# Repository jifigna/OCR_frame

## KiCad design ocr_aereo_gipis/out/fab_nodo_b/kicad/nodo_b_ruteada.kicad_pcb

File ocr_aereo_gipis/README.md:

# OCR Aéreo — versión GIPIS (definitiva, 2026-10-20)

Placa del nodo aéreo/bote: Heltec WiFi LoRa 32 V4 + OCR 0222 Ed (por UART MUX 2 click)
+ PAR 231 (por ADS1115) + inclinación (ICM-20689) + respaldo en microSD + alimentación
de batería de 12 V con buck D-SUN. Para la campaña CONAE (SABIA-Mar), octubre 2026.

Diseñada para fabricar en la **LPKF ProtoMat S63** del laboratorio: **una sola cara**
(todo el cobre abajo, B.Cu), **sin puentes**, sin metalizado. Los zócalos se sueldan
solo del lado del cobre.

| | |
|---|---|
| Placa | 104 × 90 mm, FR4 1,6 mm |
| Pistas | 0,92 mm (señal) / 1,38 mm (potencia), mínimo 0,8 |
| Aislación | 0,6 mm entre pistas, 0,5 mm entre plano de GND y pistas |
| Borde | 1 mm |
| DRC | 0 errores, 0 pads sin conectar, esquemático ↔ PCB en paridad |

## Conexiones principales

- **I2C en GPIO17/18** (bus del OLED, como en el protoboard), por los pads auxiliares
  de la V4 en el extremo opuesto al USB, del lado de J2. ADS1115 en 0x48, ICM-20689
  en 0x68 (AD0 a GND).
- **OCR**: TX del click → GPIO6 (J3.17). Click en canal 1 (A0/A1 a GND).
- **microSD (HW-125, 5 V)**: CS 42, SCK 41, MOSI 40, MISO 39.
- **Alimentación**: 12 V → fusible → 1N5819 → D-SUN (~5,3 V) → JP1 → 1N5819 → +5V
  (Heltec y SD). ADS1115 desde Ve; ICM y click desde 3V3 (J3.3).
- **Borneras** de 2 polos, paso 5,08: J1 batería, J2 alimentación del OCR,
  J3 alimentación del PAR, J4 señal del PAR. La bornera del click da al borde izquierdo.

## Antes de fresar

Imprimir `out/fab_nodo_b/plantilla_1a1_armado.pdf` al 100 % (sin "ajustar a página")
y apoyar los módulos reales. **Sin medir todavía**: la posición de los pads auxiliares
GPIO17/18 de la Heltec y el paso de las borneras. Ver `out/fab_nodo_b/LEEME.txt`.

## Archivos

- `nodo_b_ruteada.kicad_pro` — proyecto KiCad 10 (PCB ruteado + esquemático + librerías
  del proyecto `nodo_b.pretty` / `nodo_b.kicad_sym` + modelos 3D en `3d/`).
- `out/fab_nodo_b/` (y `.zip`) — paquete de fabricación: Gerber, Excellon, plantillas 1:1,
  LEEME con mechas.
- `out/` — esquemático en PDF, imágenes del ruteo y 3D, reporte de DRC.

## Regenerar

Todo sale de scripts (no editar el PCB a mano: se pisa al regenerar):

```
./make.sh
```

`gen_board.py` (ubicación, footprints y pre-ruteos fijos) → `route.py` (Freerouting:
una cara, GND ruteado) → `plano_gnd.py` → `gen_sch.py` + `finalizar.py` (esquemático
y librerías) → DRC → `fab_javi.py` (paquete de fabricación). Requiere KiCad 10 con
Python (`pcbnew`), Java y Freerouting 2.4.1 (`FREEROUTING_JAR` para indicar dónde está
el `.jar`; por defecto `~/.local/share/freerouting/freerouting-2.4.1.jar`).

GIPIS — UNPSJB.

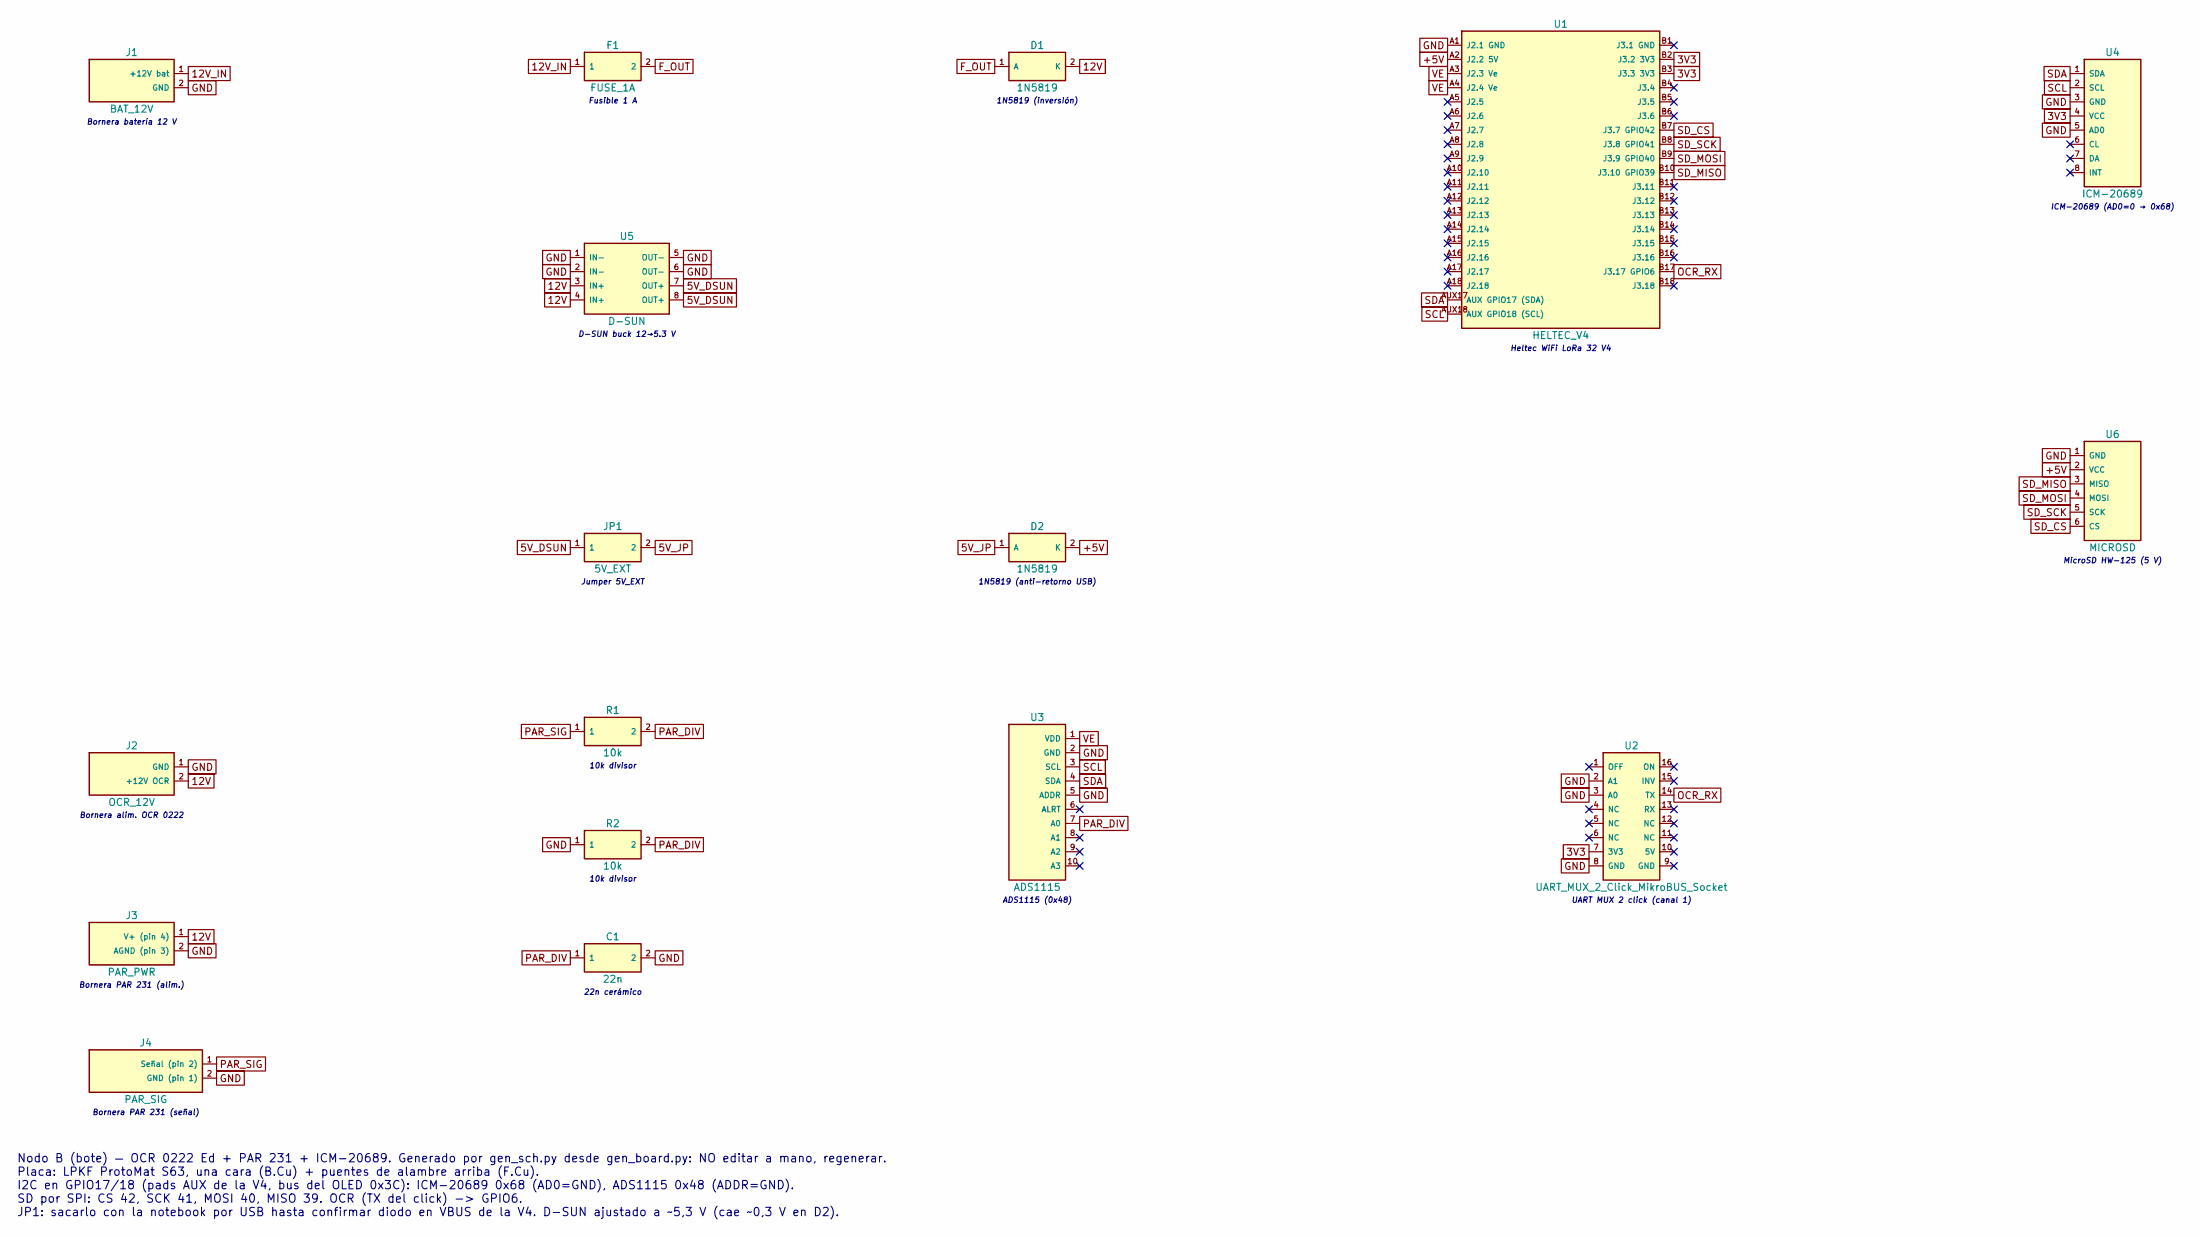
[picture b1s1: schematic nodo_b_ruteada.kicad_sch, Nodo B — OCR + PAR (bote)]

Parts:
C1: 22n
D1, D2: 1N5819
F1: FUSE_1A
J1: BAT_12V
J2: OCR_12V
J3: PAR_PWR
J4: PAR_SIG
JP1: 5V_EXT
R1, R2: 10k
U1: HELTEC_V4
U2: UART_MUX_2_Click_MikroBUS_Socket
U3: ADS1115
U4: ICM-20689
U5: D-SUN
U6: MICROSD

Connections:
3V3: U1.B2 (J3.2 3V3), U1.B3 (J3.3 3V3), U2.7 (3V3), U4.4 (VCC)
5V_DSUN: JP1.1, U5.7 (OUT+), U5.8 (OUT+)
5V_JP: D2.1 (A), JP1.2
12V: D1.2 (K), J2.2 (+12V OCR), J3.1 (V+ (pin 4)), U5.3 (IN+), U5.4 (IN+)
12V_IN: F1.1, J1.1 (+12V bat)
+5V: D2.2 (K), U1.A2 (J2.2 5V), U6.2 (VCC)
F_OUT: D1.1 (A), F1.2
GND: C1.2, J1.2 (GND), J2.1 (GND), J3.2 (AGND (pin 3)), J4.2 (GND (pin 1)), R2.1, U1.A1 (J2.1 GND), U2.2 (A1), U2.3 (A0), U2.8 (GND), U3.2 (GND), U3.5 (ADDR), U4.3 (GND), U4.5 (AD0), U5.1 (IN−), U5.2 (IN−), U5.5 (OUT−), U5.6 (OUT−), U6.1 (GND)
OCR_RX: U1.B17 (J3.17 GPIO6), U2.14 (TX)
PAR_DIV: C1.1, R1.2, R2.2, U3.7 (A0)
PAR_SIG: J4.1 (Señal (pin 2)), R1.1
SCL: U1.AUX18 (AUX GPIO18 (SCL)), U3.3 (SCL), U4.2 (SCL)
SDA: U1.AUX17 (AUX GPIO17 (SDA)), U3.4 (SDA), U4.1 (SDA)
SD_CS: U1.B7 (J3.7 GPIO42), U6.6 (CS)
SD_MISO: U1.B10 (J3.10 GPIO39), U6.3 (MISO)
SD_MOSI: U1.B9 (J3.9 GPIO40), U6.4 (MOSI)
SD_SCK: U1.B8 (J3.8 GPIO41), U6.5 (SCK)
VE: U1.A3 (J2.3 Ve), U1.A4 (J2.4 Ve), U3.1 (VDD)

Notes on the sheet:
Nodo B (bote) — OCR 0222 Ed + PAR 231 + ICM-20689. Generado por gen_sch.py desde gen_board.py: NO editar a mano, regenerar. Placa: LPKF ProtoMat S63, una cara (B.Cu) + puentes de alambre arriba (F.Cu). I2C en GPIO17/18 (pads AUX de la V4, bus del OLED 0x3C): ICM-20689 0x68 (AD0=GND), ADS1115 0x48 (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
Bornera batería 12 V
Fusible 1 A
1N5819 (inversión)
Bornera alim. OCR 0222
Bornera PAR 231 (alim.)
Bornera PAR 231 (señal)
10k divisor
22n cerámico
ADS1115 (0x48)
D-SUN buck 12→5.3 V
Jumper 5V_EXT
1N5819 (anti-retorno USB)
Heltec WiFi LoRa 32 V4
ICM-20689 (AD0=0 → 0x68)
UART MUX 2 click (canal 1)
MicroSD HW-125 (5 V)

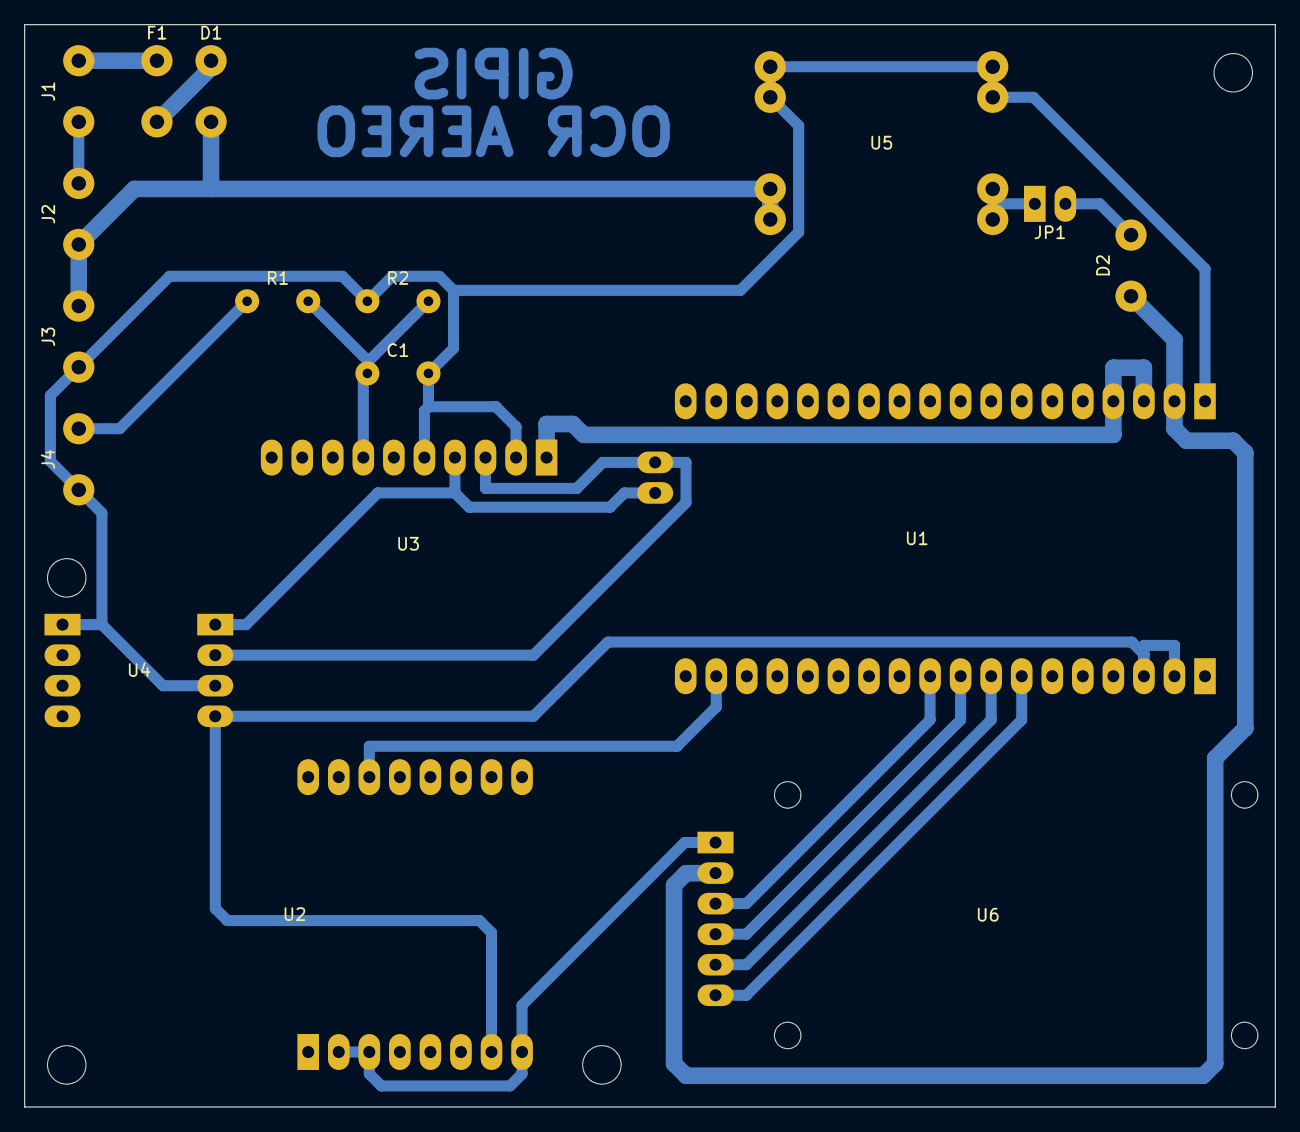
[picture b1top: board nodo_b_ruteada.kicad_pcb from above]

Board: 2 copper layers, 104.0 x 90.0 mm, 21 parts (0 on the bottom side), 18 nets.

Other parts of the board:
H1, H2, H3, H4: M3

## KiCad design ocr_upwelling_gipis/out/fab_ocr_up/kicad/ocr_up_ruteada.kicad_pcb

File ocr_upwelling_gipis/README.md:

# OCR Upwelling — versión GIPIS v2 (2026-10-20)

Placa del nodo del frame (OCR que mira al mar, Lu): Heltec WiFi LoRa 32 V4 + OCR por
RS-232 (MAX3232) + inclinación (ICM-20689 y GY-511) + RTC (ZS-042) + respaldo en microSD
+ buck desde la batería de 12 V. Campaña CONAE (SABIA-Mar), octubre 2026.

Parte de la placa de Juan (`OCR_AEREO_HELTEC_V1` en `main`): misma placa de 109,5 × 85,5 mm
y misma ubicación de módulos, con las correcciones de la revisión
(`REVISION_placa_juan_20261020.md`) y **sin relés ni BioShutter** (el OCR toma 12 V directo).

Para la **LPKF ProtoMat S63** del laboratorio: **una sola cara** (todo el cobre abajo),
sin metalizado, sin vías. Lo que no se puede rutear en una cara va con **8 puentes de
alambre W1–W8** (componentes de 2 pads; en el esquemático y en la plantilla).

| | |
|---|---|
| Pistas | 0,92 mm (señal) / 1,38 mm (potencia), mínimo 0,65 entre pines vecinos |
| Aislación | 0,6 mm entre pistas, 0,5 mm entre plano de GND y pistas, borde 1 mm |
| DRC | 0 errores, 0 pads sin conectar, esquemático ↔ PCB en paridad |

## Cambios respecto de la placa de Juan

- Tiras de la Heltec a 22,86 mm y alineadas (estaban a 23,00 y corridas 0,5 mm).
- I2C en GPIO17/18 (pads AUX del lado de J2), como en el protoboard.
- SD en GPIO 39–42 (CS 42, SCK 41, MOSI 40, MISO 39): el 21 es el reset del OLED y el 26
  lo usa la PSRAM.
- ICM-20689 con AD0 a Vext → 0x69 (en 0x68 chocaba con el DS3231) y tiras a 12,70 mm.
- MAX3232 girado 180°; T2IN a GND. UART: GPIO5 → T1IN, R1OUT → GPIO6.
- Fusible a la ENTRADA de los 12 V; D1 Schottky 1N5822; zener 1N5339B (5,6 V) sobre +5V;
  C7 470 µF con footprint de Ø8.
- Buck: J11 IN+, J10 IN− (GND), J8 OUT+ (5 V), J9 OUT− (GND).
- +5V → JP1 → D3 1N5819 → pin 5V de la Heltec (sacar JP1 con la Heltec por USB).
- Borneras Phoenix MCV 5,08: J7 batería (abajo) y J6 OCR en el borde derecho
  (de arriba a abajo GND, RX, TX, +12V).

## Antes de fresar

Imprimir `out/fab_ocr_up/plantilla_1a1_armado.pdf` al 100 % y apoyar los módulos reales.
Sin medir todavía: los pads AUX 17/18 de la Heltec, el orden de pines de la SD (Juan tenía
GND arriba) y del GY-511. Ver `out/fab_ocr_up/LEEME.txt`.

## Regenerar

Todo sale de scripts (no editar el PCB a mano: se pisa al regenerar): `./make.sh`.
`gen_board.py` (ubicación, footprints y pre-ruteos fijos) → `route.py` (Freerouting) →
`plano_gnd.py` → `fix_islas.py` → `convertir_alambres.py` (los tramos de arriba pasan a ser
puentes de alambre W6…, con `jumper_pad_groups`) → `esquema.py` / `gen_sch.py` /
`finalizar.py` → DRC → `fab_javi.py`. Requiere KiCad 10 con Python (`pcbnew`) y
Freerouting 2.4.1 (Java 25). `FREEROUTING_HOST=usuario@host` corre Freerouting en otra
máquina por SSH (en un contenedor `eclipse-temurin:25-jre`); vacío, lo corre local.

GIPIS — UNPSJB.

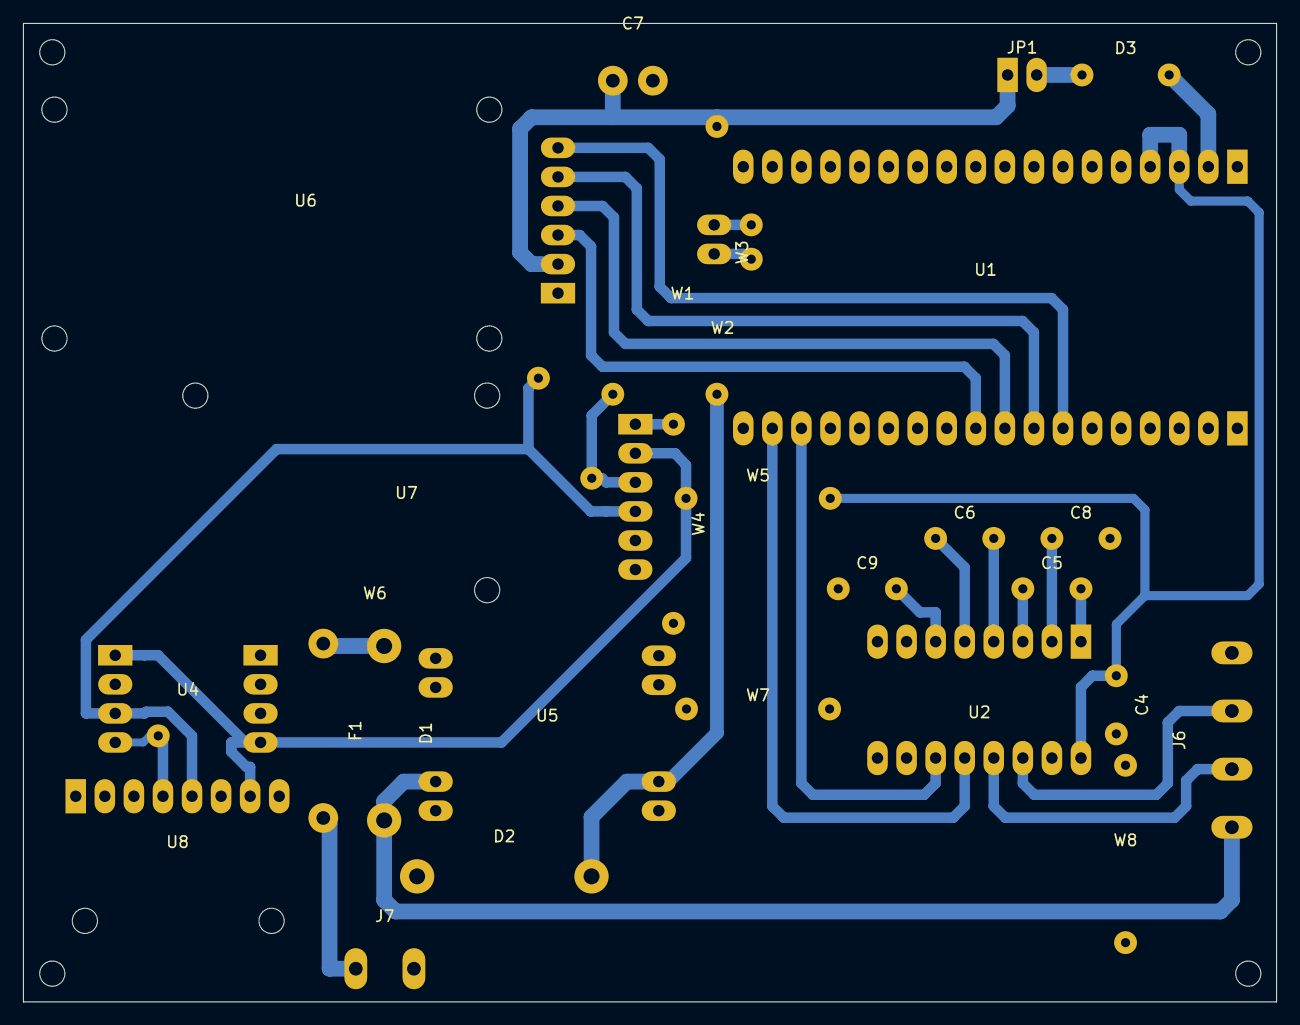
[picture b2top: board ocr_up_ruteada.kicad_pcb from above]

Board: 2 copper layers, 109.5 x 85.5 mm, 32 parts (0 on the bottom side), 29 nets.

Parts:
C4, C5, C6, C8, C9: 100n
C7: 470uF
D1: 1N5822
D2: 1N5339B
D3: 1N5819
F1: FUSE_2A
H1, H2, H3, H4: M2
J6: OCR
J7: BATERIA
JP1: 5V_EXT
U1: HELTEC_V4
U2: MAX3232
U4: ICM-20689
U5: BUCK
U6: MICROSD
U7: RTC_ZS-042
U8: GY-511
W1: PUENTE_SCL
W2: PUENTE_SDA
W3: PUENTE_5V
W4: PUENTE_GND
W5: PUENTE_VE
W6, W7, W8: ALAMBRE

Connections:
5V_HEL: D3.2, U1.A2
5V_JP: D3.1, JP1.2
5V_TOP: C7.1, JP1.1, U6.2, W3.1
12V: D1.2, J6.4, U5.3
+5V: D2.1, U5.7, W3.2
BATERIA: F1.2, J7.2
F_OUT: D1.1, F1.1
GND: C4.2, C7.2, C8.2, C9.1, D2.2, J6.1, J7.1, U1.A1, U2.10, U2.15, U4.2, U5.6, U6.1, U8.6, W4.2, W7.1, W7.2, W8.1, W8.2
GND_RTC: U7.1, W4.1
H_RX: U1.B17, U2.12
H_TX: U1.B16, U2.11
MAX_C1N: C5.1, U2.3
MAX_C1P: C5.2, U2.1
MAX_C2N: C6.1, U2.5
MAX_C2P: C6.2, U2.4
MAX_VSN: C9.2, U2.6
MAX_VSP: C8.1, U2.2
RX_OCR: J6.2, U2.14
SCL: U1.AUX18, W1.1
SCL_B: U4.3, U7.4, U8.5, W1.2
SDA: U1.AUX17, W2.1
SDA_B: U4.4, U7.3, U8.4, W2.2, W6.1, W6.2
SD_CS: U1.B7, U6.6
SD_MISO: U1.B10, U6.3
SD_MOSI: U1.B9, U6.4
SD_SCK: U1.B8, U6.5
TX_OCR: J6.3, U2.13
VE: C4.1, U1.A3, U1.A4, U2.16, W5.1
VE_B: U4.1, U4.8, U7.2, U8.7, W5.2

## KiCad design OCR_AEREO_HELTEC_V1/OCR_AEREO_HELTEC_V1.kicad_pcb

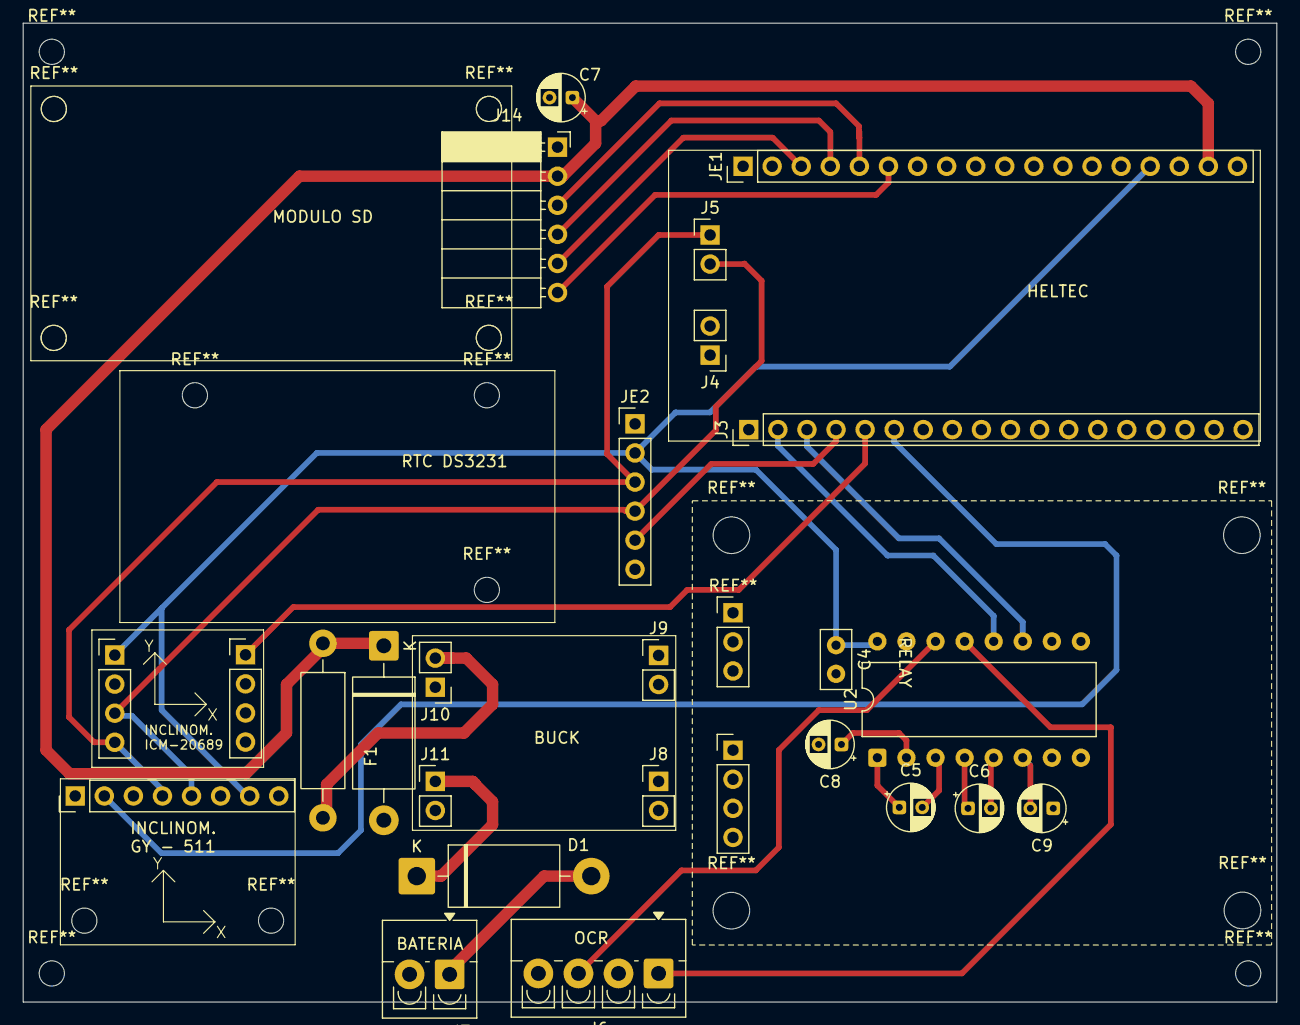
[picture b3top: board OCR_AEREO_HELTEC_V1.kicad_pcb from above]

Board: 2 copper layers, 109.5 x 85.5 mm, 26 parts (0 on the bottom side), 25 nets.

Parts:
C4: 0.1 uF; C_Disc_D5.0mm_W2.5mm_P2.50mm
C5, C6, C8, C9: 0.1uF; CP_Radial_D4.0mm_P2.00mm
C7: 470uF; CP_Radial_D4.0mm_P2.00mm
D1: 1N5402; D_DO-201AD_P15.24mm_Horizontal
D2: 1N53xxB; D_DO-201_P15.24mm_Horizontal
F1: Fuse; R_Axial_DIN0411_L9.9mm_D3.6mm_P15.24mm_Horizontal
J1, J1#2, J2: Conn_01x04_Socket; PinHeader_1x04_P2.54mm_Vertical
J3: Conn_01x18_Pin; PinHeader_1x18_P2.54mm_Vertical
J4, J5, J8, J9, J10, J11: Conn_01x02_Pin; PinHeader_1x02_P2.54mm_Vertical
J6: OCR; TerminalBlock_4Ucon_1x04_P3.50mm_Vertical
J7: BATERÍA; TerminalBlock_4Ucon_1x02_P3.50mm_Vertical
J12: Conn_01x08_Socket; PinHeader_1x08_P2.54mm_Vertical
J14: MODULO SD; PinSocket_1x06_P2.54mm_Horizontal
JE1: Conn_01x18_Pin; PinHeader_1x18_P2.54mm_Vertical
JE2: RTC_DS3231; PinHeader_1x06_P2.54mm_Vertical
U2: MAX3232; DIP-16_W10.16mm

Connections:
5V: C7.1, D2.1 (K), F1.1, J14.2, JE1.17
BATERIA: D1.2 (A), J7.1
CLK_SPI: J14.5, JE1.3
CS_SD: J14.6, JE1.6
GND: C4.2, C7.2, C8.2, C9.1, D2.2 (A), J1#2.2, J2.4, J3.18, J6.2, J7.2, J8.1 (Pin_1_1), J9.2 (Pin_2_2), J12.6, J14.1, JE2.1, U2.15 (GND)
HELTEC_TO_OCR: J3.3, U2.11 (T1IN)
INT_INCL_1: J2.1, J3.5
INT_INCL_2: J3.6, J12.2
IN_BUCK: D1.1 (K), J11.1 (Pin_1_1)
MISO: J14.3, JE1.5
MOSI: J14.4, JE1.4
unnamed: C5.1, U2.1 (C1+)
unnamed: C5.2, U2.3 (C1-)
unnamed: C6.1, U2.4 (C2+)
unnamed: C6.2, U2.5 (C2-)
unnamed: C8.1, U2.2 (VS+)
unnamed: C9.2, U2.6 (VS-)
OCR_TO_HELTEC: J3.2, U2.12 (R1OUT)
OUT_BUCK: F1.2, J10.2 (Pin_2_2)
RX_OCR: J6.3, U2.14 (T1OUT)
SCL: J1#2.3, J5.2, J12.5, JE2.4
SDA: J1#2.4, J5.1, J12.4, JE2.3
SQW: J3.4, JE2.5
TX_OCR: J6.1, U2.13 (R1IN)
Vext: C4.1, J1#2.1, J12.7, JE1.15, JE2.2, U2.16 (VCC)

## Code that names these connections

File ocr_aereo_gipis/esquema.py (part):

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    'U6': dict(zip(map(str, range(1, 7)), ['GND', 'VCC', 'MISO', 'MOSI', 'SCK', 'CS'])),
}
HELTEC_J2 = {1: 'GND', 2: '5V', 3: 'Ve', 4: 'Ve'}
HELTEC_J3 = {1: 'GND', 2: '3V3', 3: '3V3', 7: 'GPIO42', 8: 'GPIO41', 9: 'GPIO40', 10: 'GPIO39', 17: 'GPIO6'}
PIN['U1'] = {}
for n in range(1, 19):
    PIN['U1'][f'A{n}'] = f'J2.{n} ' + HELTEC_J2.get(n, '')
    PIN['U1'][f'B{n}'] = f'J3.{n} ' + HELTEC_J3.get(n, '')
PIN['U1']['AUX17'] = 'AUX GPIO17 (SDA)'
PIN['U1']['AUX18'] = 'AUX GPIO18 (SCL)'

TITULO = {
    'J1': 'Bornera batería 12 V', 'F1': 'Fusible 1 A', 'D1': '1N5819 (inversión)',
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    ], 128)
    nota(146, 236, [
        'Señales',
        'I2C (bus del OLED): SDA = GPIO17, SCL = GPIO18 (pads AUX) → ADS1115 0x48 + ICM-20689 0x68.',
        'SD (SPI): CS 42 · SCK 41 · MOSI 40 · MISO 39.',
        'OCR: la señal RS-232 entra por la bornera del propio click (cable, no PCB);',
        'TX del click → GPIO6. A0/A1 = GND → canal 1. PAR 0–5 V → R1/R2 → 0–2.5 V a A0.',
    ], 132)
    nota(284, 236, [
        'Fabricación (LPKF, doble faz sin metalizar)',
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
